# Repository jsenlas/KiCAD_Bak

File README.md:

# KiCAD_Bak
Bachelor thesis HW section - KiCAD

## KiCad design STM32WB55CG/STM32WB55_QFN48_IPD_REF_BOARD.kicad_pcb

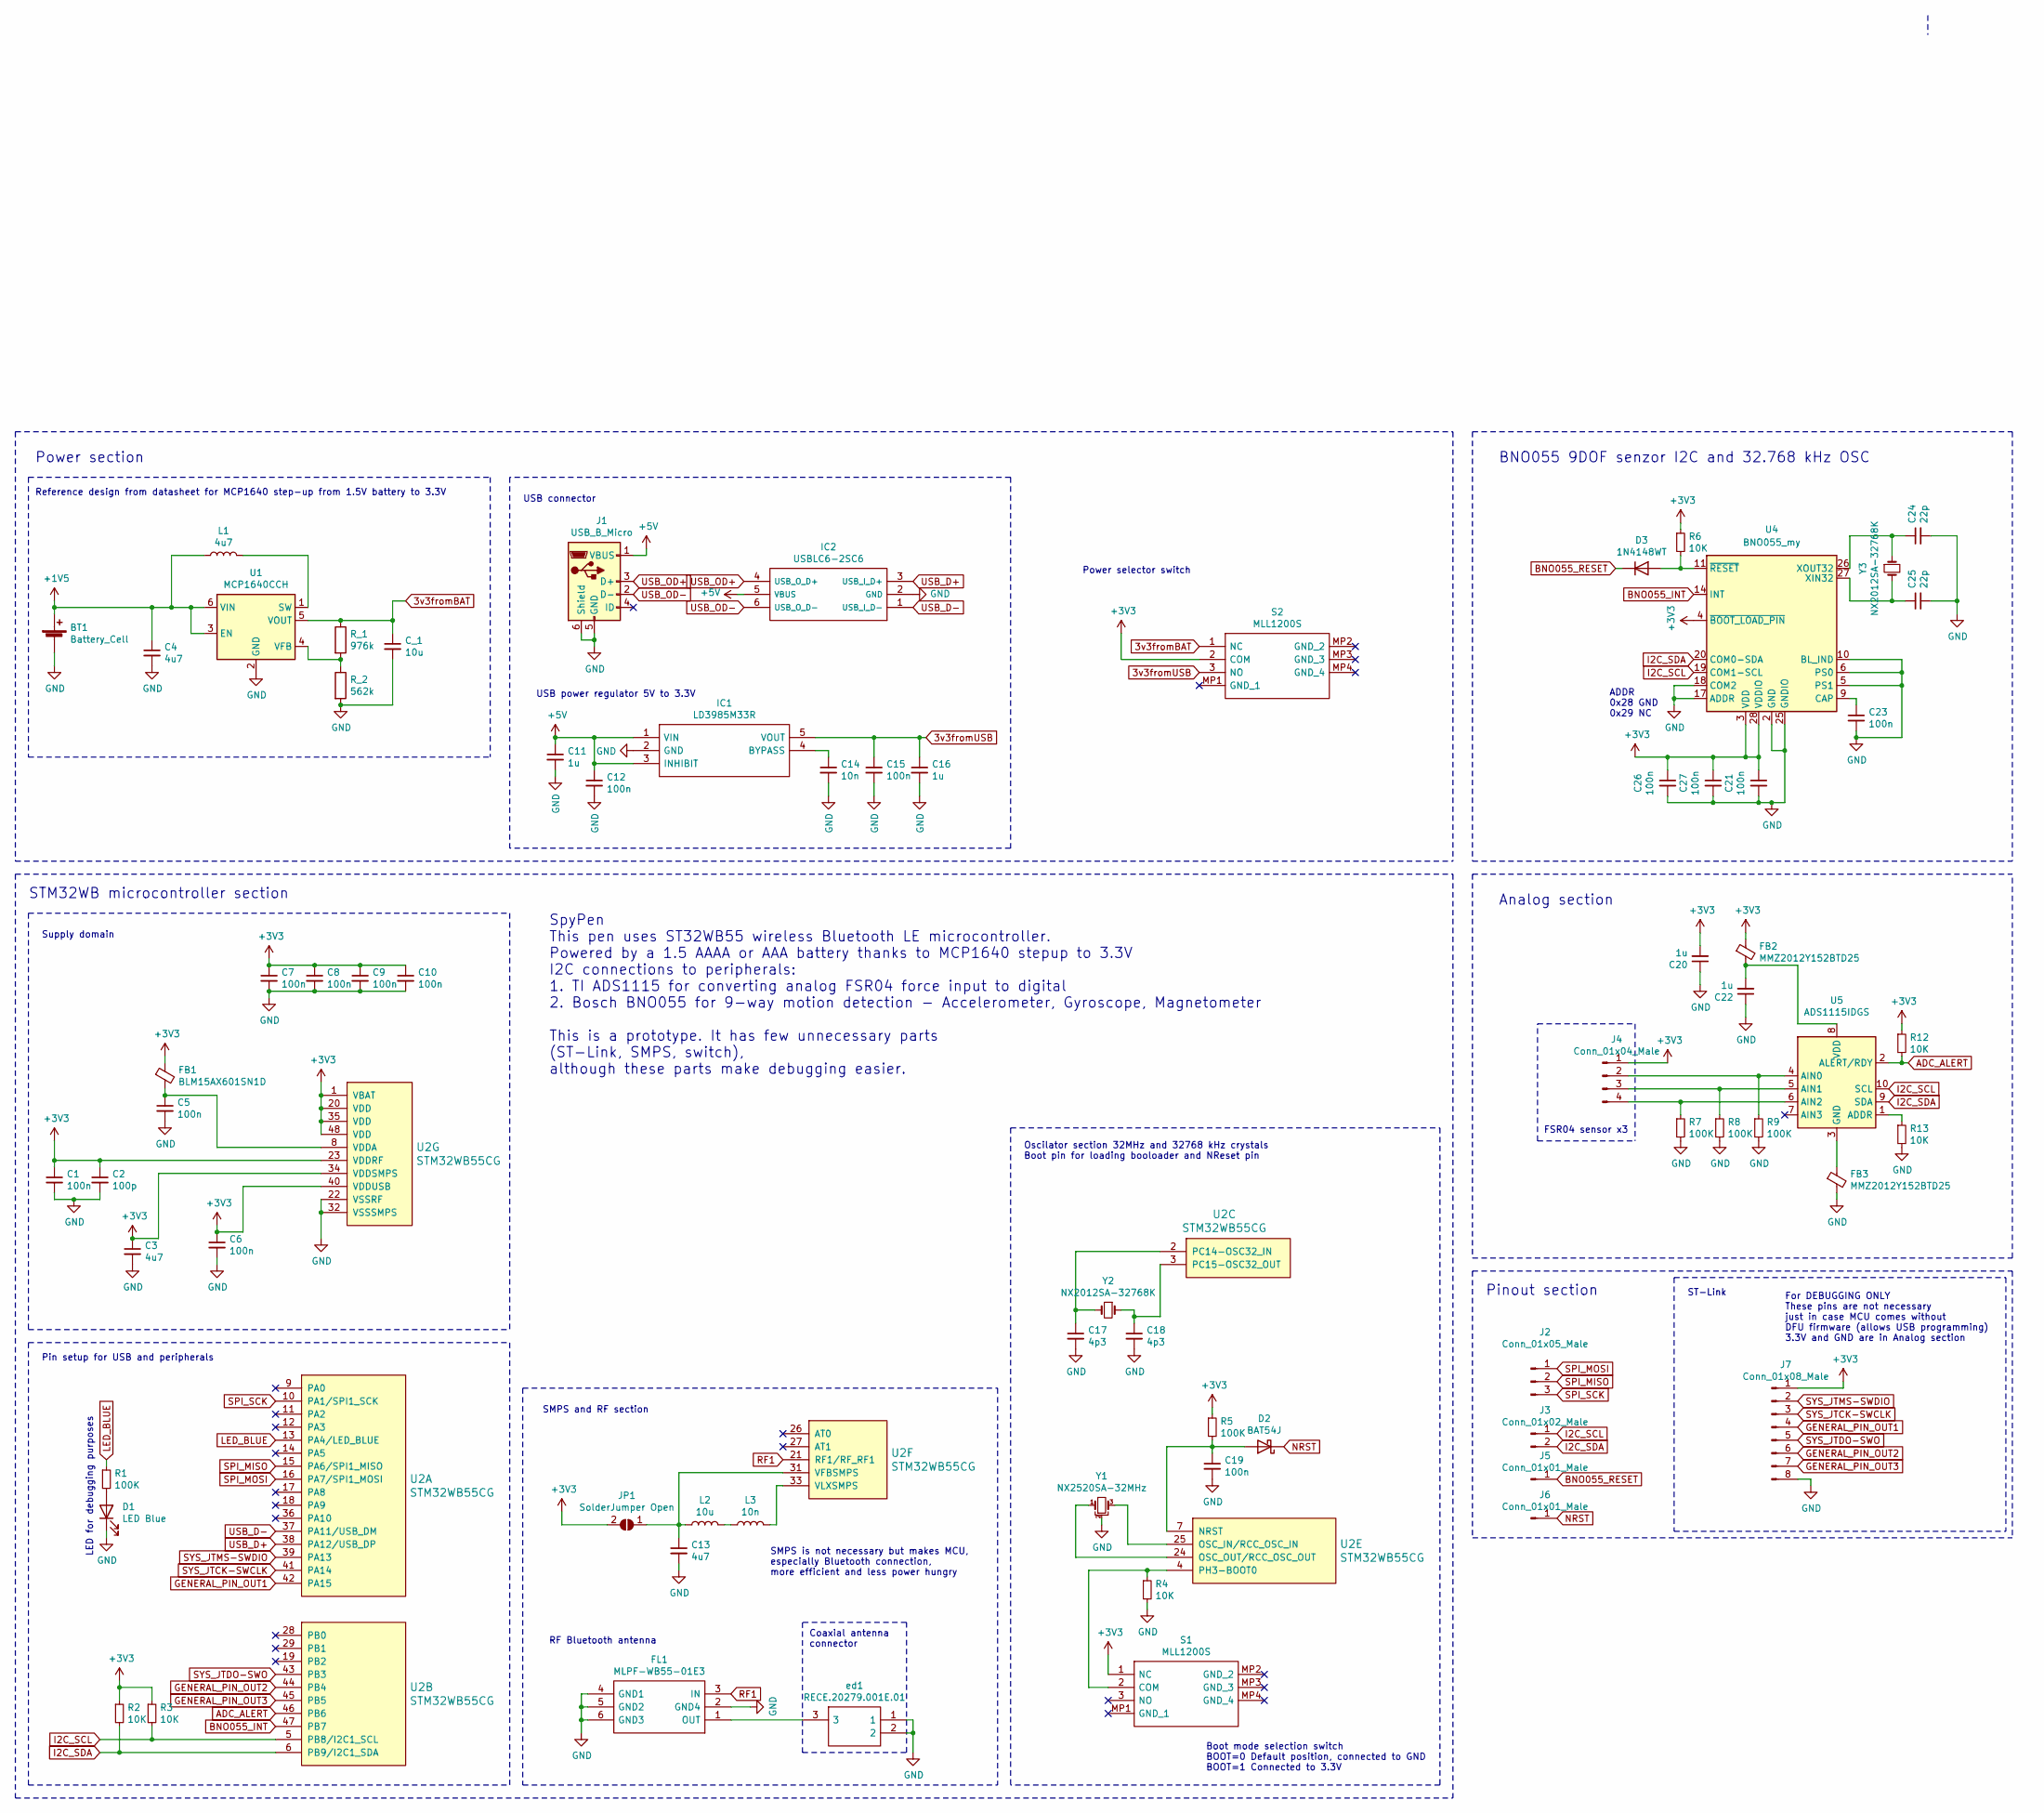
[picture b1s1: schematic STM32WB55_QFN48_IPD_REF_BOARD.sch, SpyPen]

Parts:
BT1: Battery_Cell; battery_connector_narrow
C1, C5, C6, C7, C8, C9, C10, C15, C19, C21, C23, C26, C27: 100n; C_0402_1005Metric
C2: 100p; C_0402_1005Metric
C3, C4, C13: 4u7; C_0402_1005Metric
C11, C16, C20, C22: 1u; C_0402_1005Metric
C12: 100n; C_0603_1608Metric
C14: 10n; C_0402_1005Metric
C17, C18: 4p3; C_0402_1005Metric
C24, C25: 22p; C_0402_1005Metric
C_1: 10u; C_0402_1005Metric
D1: LED Blue; LED_0603_1608Metric
D2: BAT54J; D_SOD-323F
D3: 1N4148WT; D_SOD-523
FB1: BLM15AX601SN1D; R_0402_1005Metric
FB2, FB3: MMZ2012Y152BTD25; R_0402_1005Metric
FL1: MLPF-WB55-01E3; MLPF-WB55-02E3; Manufacturer_Part_Number MLPF-WB55-01E3; Mouser Part Number 511-MLPF-WB55-01E3
IC1: LD3985M33R; SOT-23-5; Manufacturer_Part_Number LD3985M33R; Mouser Part Number 511-LD3985M33R
IC2: USBLC6-2SC6; SOT-23-6; Manufacturer_Part_Number USBLC6-2SC6; Mouser Part Number 511-USBLC6-2SC6
J1: USB_B_Micro; UB-MC5BR3-SDWP604-4S-TF
J2: Conn_01x05_Male; pin_03
J3: Conn_01x02_Male; pin_02
J4: Conn_01x04_Male; Pin_FSR
J5, J6: Conn_01x01_Male; pin_01
J7: Conn_01x08_Male; pin_08
JP1: SolderJumper Open; SolderJumper-2_P1.3mm_Open_TrianglePad1.0x1.5mm
L1: 4u7; L_0603_1608Metric
L2: 10u; L_0712_SMD
L3: 10n; L_0603_1608Metric
R1, R5, R7, R8, R9: 100K; R_0402_1005Metric
R2, R3, R4, R6, R12, R13: 10K; R_0402_1005Metric
R_1: 976k; R_0402_1005Metric
R_2: 562k; R_0402_1005Metric
S1, S2: MLL1200S; Manufacturer_Part_Number MLL1200S; Mouser Part Number 506-MLL1200S
U1: MCP1640CCH; SOT-23-6
U2: STM32WB55CG; STM32WB55CGU7
U4: BNO055_my; LGA-28_5.2x3.8mm_P0.5mm
U5: ADS1115IDGS; ADS1115IRUGR
Y1: NX2520SA-32MHz; Crystal_SMD_2520-4Pin_2.5x2.0mm
Y2, Y3: NX2012SA-32768K; Crystal_2012_custom
ed1: RECE.20279.001E.01; Manufacturer_Part_Number RECE.20279.001E.01; Mouser Part Number N/A

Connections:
3v3fromBAT: C_1.1, R_1.1, S2.1 (NC), U1.5 (VOUT)
3v3fromUSB: C15.1, C16.1, IC1.5 (VOUT), S2.3 (NO)
+1V5: BT1.1 (+), C4.1, L1.1, U1.3 (EN), U1.6 (VIN)
+3V3: C1.1, C2.1, C3.1, C6.1, C7.1, C8.1, C9.1, C10.1, C20.2, C21.1, C26.1, C27.1, FB1.1, FB2.1, J4.1, J7.1, JP1.2 (B), R2.1, R3.1, R5.1, R6.1, R12.1, S1.1 (NC), S2.2 (COM), U2.1 (VBAT), U2.20 (VDD), U2.23 (VDDRF), U2.34 (VDDSMPS), U2.35 (VDD), U2.40 (VDDUSB), U2.48 (VDD), U4.3 (VDD), U4.4 (~BOOT_LOAD_PIN), U4.28 (VDDIO)
+5V: C11.1, C12.1, IC1.1 (VIN), IC1.3 (INHIBIT), IC2.5 (VBUS), J1.1 (VBUS)
ADC_ALERT: R12.2, U2.46 (PB6), U5.2 (ALERT/RDY)
BNO055_INT: U2.47 (PB7), U4.14 (INT)
BNO055_RESET: D3.1 (K), J5.1
GENERAL_PIN_OUT1: J7.4, U2.42 (PA15)
GENERAL_PIN_OUT2: J7.6, U2.44 (PB4)
GENERAL_PIN_OUT3: J7.7, U2.45 (PB5)
GND: BT1.2 (-), C1.2, C2.2, C3.2, C4.2, C5.2, C6.2, C7.2, C8.2, C9.2, C10.2, C11.2, C12.2, C13.2, C14.2, C15.2, C16.2, C17.2, C18.2, C19.2, C20.1, C21.2, C22.1, C23.2, C24.2, C25.2, C26.2, C27.2, C_1.2, D1.1 (K), FB3.2, FL1.2 (GND4), FL1.4 (GND1), FL1.5 (GND2), FL1.6 (GND3), IC1.2 (GND), IC2.2 (GND), J1.5 (GND), J1.6 (Shield), J7.8, R4.2, R7.2, R8.2, R9.2, R13.2, R_2.2, U1.2 (GND), U2.22 (VSSRF), U2.32 (VSSSMPS), U2.49, U4.2 (GND), U4.5 (PS1), U4.6 (PS0), U4.10 (BL_IND), U4.15 (GNDIO), U4.16 (GNDIO), U4.17 (ADDR), U4.18 (COM2), U4.25 (GNDIO), Y1.2, Y1.4, ed1.1, ed1.2
I2C_SCL: J3.1, R3.2, U2.5 (PB8/I2C1_SCL), U4.19 (COM1-SCL), U5.10 (SCL)
I2C_SDA: J3.2, R2.2, U2.6 (PB9/I2C1_SDA), U4.20 (COM0-SDA), U5.9 (SDA)
LED_BLUE: R1.1, U2.13 (PA4/LED_BLUE)
NRST: D2.1 (K), J6.1
unnamed: C5.1, FB1.2, U2.8 (VDDA)
unnamed: C13.1, JP1.1 (A), L2.1, U2.31 (VFBSMPS)
unnamed: C14.1, IC1.4 (BYPASS)
unnamed: C17.1, U2.2 (PC14-OSC32_IN), Y2.2
unnamed: C18.1, U2.3 (PC15-OSC32_OUT), Y2.1
unnamed: C19.1, D2.2 (A), R5.2, U2.7 (NRST)
unnamed: C22.2, FB2.2, U5.8 (VDD)
unnamed: C23.1, U4.9 (CAP)
unnamed: C24.1, U4.26 (XOUT32), Y3.1
unnamed: C25.1, U4.27 (XIN32), Y3.2
unnamed: D1.2 (A), R1.2
unnamed: D3.2 (A), R6.2, U4.11 (~RESET)
unnamed: FB3.1, U5.3 (GND)
unnamed: FL1.1 (OUT), ed1.3
unnamed: J4.2, R9.1, U5.4 (AIN0)
unnamed: J4.3, R8.1, U5.5 (AIN1)
unnamed: J4.4, R7.1, U5.6 (AIN2)
unnamed: L1.2, U1.1 (SW)
unnamed: L2.2, L3.1
unnamed: L3.2, U2.33 (VLXSMPS)
unnamed: R4.1, S1.2 (COM), U2.4 (PH3-BOOT0)
unnamed: R13.1, U5.1 (ADDR)
unnamed: R_1.2, R_2.1, U1.4 (VFB)
unnamed: U2.24 (OSC_OUT/RCC_OSC_OUT), Y1.1
unnamed: U2.25 (OSC_IN/RCC_OSC_IN), Y1.3
RF1: FL1.3 (IN), U2.21 (RF1/RF_RF1)
SPI_MISO: J2.2, U2.15 (PA6/SPI1_MISO)
SPI_MOSI: J2.1, U2.16 (PA7/SPI1_MOSI)
SPI_SCK: J2.3, U2.10 (PA1/SPI1_SCK)
SYS_JTCK-SWCLK: J7.3, U2.41 (PA14)
SYS_JTDO-SWO: J7.5, U2.43 (PB3)
SYS_JTMS-SWDIO: J7.2, U2.39 (PA13)
USB_D+: IC2.3 (USB_I_D+), U2.38 (PA12/USB_DP)
USB_D-: IC2.1 (USB_I_D-), U2.37 (PA11/USB_DM)
USB_OD+: IC2.4 (USB_O_D+), J1.3 (D+)
USB_OD-: IC2.6 (USB_O_D-), J1.2 (D-)

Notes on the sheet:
Analog section
USB connector
RF Bluetooth antenna
Supply domain
Oscilator section 32MHz and 32768 kHz crystals Boot pin for loading booloader and NReset pin
Pin setup for USB and peripherals
SMPS and RF section
Reference design from datasheet for MCP1640 step-up from 1.5V battery to 3.3V
USB power regulator 5V to 3.3V
Boot mode selection switch BOOT=0 Default position, connected to GND BOOT=1 Connected to 3.3V
LED for debugging purposes
Coaxial antenna connector
BNO055 9DOF senzor I2C and 32.768 kHz OSC
Pinout section
FSR04 sensor x3
For DEBUGGING ONLY These pins are not necessary just in case MCU comes without DFU firmware (allows USB programming) 3.3V and GND are in Analog section
ST-Link
SMPS is not necessary but makes MCU, especially Bluetooth connection, more efficient and less power hungry
STM32WB microcontroller section
Power section
Power selector switch
SpyPen This pen uses ST32WB55 wireless Bluetooth LE microcontroller. Powered by a 1.5 AAAA or AAA battery thanks to MCP1640 stepup to 3.3V I2C connections to peripherals: 1. TI ADS1115 for converting analog FSR04 force input to digital 2. Bosch BNO055 for 9-way motion detection - Accelerometer, Gyr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
ADDR 0x28 GND 0x29 NC

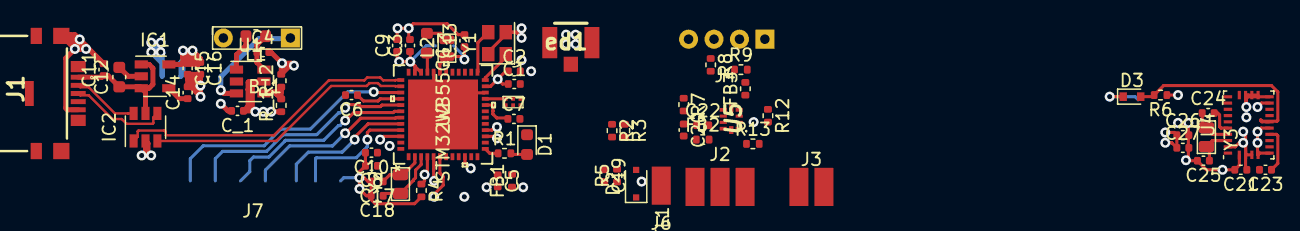
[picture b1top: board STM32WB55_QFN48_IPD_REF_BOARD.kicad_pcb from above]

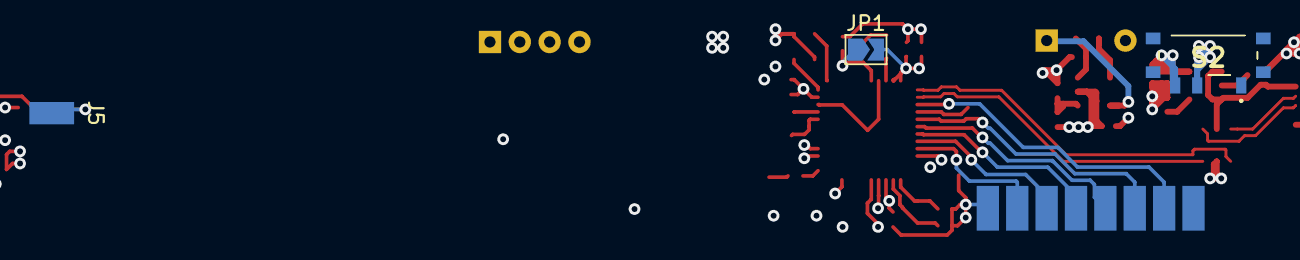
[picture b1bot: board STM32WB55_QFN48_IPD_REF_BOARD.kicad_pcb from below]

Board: 4 copper layers, 71 parts (3 on the bottom side), 52 nets.

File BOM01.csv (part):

"Source:","/home/jakub/VUT_FIT/bakalarka2.0/KiCAD_Bak/STM32WB55CG/STM32WB55_QFN48_IPD_REF_BOARD.sch"
"Date:","Wed 17 Feb 2021 11:01:06 PM CET"
"Tool:","Eeschema 5.1.9-1.fc32"
"Component Count:","70"
"Ref","Value","Footprint","Datasheet","Manufacturer","Vendor"
"BT1","Battery_Cell","0Pretty:battery_connector","~","",""
"C1","100n","Capacitor_SMD:C_0402_1005Metric","https://www.mouser.sk/ProductDetail/Yageo/CC0402JRX7R8BB104/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","",""
"C2","100p","Capacitor_SMD:C_0402_1005Metric","https://www.mouser.sk/ProductDetail/AVX/04026C101KAT2A/?qs=n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","",""
"C3","4u7","Capacitor_SMD:C_0402_1005Metric","https://www.mouser.sk/ProductDetail/Murata-Electronics/GRT15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","",""
"C4","4u7","Capacitor_SMD:C_0402_1005Metric","https://www.mouser.sk/ProductDetail/Murata-Electronics/GRT15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","",""
"C5","100n","Capacitor_SMD:C_0402_1005Metric","https://www.mouser.sk/ProductDetail/Yageo/CC0402JRX7R8BB104/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","",""
"C6","100n","Capacitor_SMD:C_0402_1005Metric","https://www.mouser.sk/ProductDetail/Yageo/CC0402JRX7R8BB104/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","",""
"C7","100n","Capacitor_SMD:C_0402_1005Metric","https://www.mouser.sk/ProductDetail/Yageo/CC0402JRX7R8BB104/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","",""
"C8","100n","Capacitor_SMD:C_0402_1005Metric","https://www.mouser.sk/ProductDetail/Yageo/CC0402JRX7R8BB104/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","",""
"C9","100n","Capacitor_SMD:C_0402_1005Metric","https://www.mouser.sk/ProductDetail/Yageo/CC0402JRX7R8BB104/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","",""
"C10","100n","Capacitor_SMD:C_0402_1005Metric","https://www.mouser.sk/ProductDetail/Yageo/CC0402JRX7R8BB104/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","",""
"C11","1u","Capacitor_SMD:C_0402_1005Metric","https://www.mouser.sk/ProductDetail/Taiyo-Yuden/LMK105BJ105M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","",""
"C12","100n","Capacitor_SMD:C_0603_1608Metric","https://www.mouser.sk/ProductDetail/Yageo/CC0201KRX6S6BB104/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","",""
"C13","4u7","Capacitor_SMD:C_0402_1005Metric","https://www.mouser.sk/ProductDetail/Murata-Electronics/GRT15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","",""
"C14","10n","Capacitor_SMD:C_0402_1005Metric","https://www.mouser.sk/ProductDetail/Murata-Electronics/GCB15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","",""
"C15","100n","Capacitor_SMD:C_0402_1005Metric","https://www.mouser.sk/ProductDetail/AVX/04026D104KAT2A/?qs=L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","",""
"C16","1u","Capacitor_SMD:C_0402_1005Metric","https://www.mouser.sk/ProductDetail/Taiyo-Yuden/LMK105BJ105M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","",""
"C17","4p3","Capacitor_SMD:C_0402_1005Metric","https://www.mouser.sk/ProductDetail/KEMET/C0402C439B5GACTU/?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","",""
"C18","4p3","Capacitor_SMD:C_0402_1005Metric","https://www.mouser.sk/ProductDetail/KEMET/C0402C439B5GACTU/?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","",""
"C19","100n","Capacitor_SMD:C_0402_1005Metric","https://www.mouser.sk/ProductDetail/Yageo/CC0402JRX7R8BB104/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","",""
"C20","1u","Capacitor_SMD:C_0402_1005Metric","https://www.mouser.sk/ProductDetail/Murata-Electronics/GRT15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","",""
"C21","100n","Capacitor_SMD:C_0402_1005Metric","https://www.mouser.sk/ProductDetail/Yageo/CC0402JRX7R8BB104/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","",""
"C22","1u","Capacitor_SMD:C_0402_1005Metric","https://www.mouser.sk/ProductDetail/Murata-Electronics/GRT15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","",""
"C23","1u","Capacitor_SMD:C_0402_1005Metric","https://www.mouser.sk/ProductDetail/Murata-Electronics/GRT15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","",""
"C24","22p","Capacitor_SMD:C_0402_1005Metric","https://www.mouser.sk/ProductDetail/KEMET/C0402C220J5GAC7411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","",""
"C25","22p","Capacitor_SMD:C_0402_1005Metric","https://www.mouser.sk/ProductDetail/KEMET/C0402C220J5GAC7411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","",""
"C_1","10u","Capacitor_SMD:C_0402_1005Metric","https://www.mouser.sk/ProductDetail/Murata-Electronics/GRJ15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","",""
"D1","LED Blue","LED_SMD:LED_0402_1005Metric","https://www.mouser.sk/ProductDetail/ROHM-Semiconductor/SMLP1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","",""
"D2","BAT54J","Diode_SMD:D_SOD-323F","https://assets.nexperia.com/documents/data-sheet/BAT54J.pdf","",""
"D3","1N4148WT","Diode_SMD:D_SOD-523","https://www.diodes.com/assets/Datasheets/ds30396.pdf","",""
"ed1","RECE.20279.001E.01","RECE_antena_connector:RECE.20279.001E.01","http://www.taoglas.com/wp-content/uploads/2016/04/RECE.20279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","",""
"FB1","Z0805C601BSMST","Resistor_SMD:R_0805_2012Metric","https://www.mouser.sk/ProductDetail/KEMET/Z0805C601BSMST/?qs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","",""
"FB2","MMZ2012Y152BTD25","Resistor_SMD:R_0805_2012Metric","https://www.mouser.sk/ProductDetail/TDK/MMZ2012Y152BTD25?qs=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","",""
"FB3","MMZ2012Y152BTD25","Resistor_SMD:R_0805_2012Metric","https://www.mouser.sk/ProductDetail/TDK/MMZ2012Y152BTD25?qs=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","",""
"FL1","MLPF-WB55-01E3","0Pretty:MLPF-WB55-02E3","https://www.st.com/resource/en/datasheet/mlpf-wb55-01e3.pdf","",""
"IC1","LD3985M33R","Package_TO_SOT_SMD:SOT-23-5","http://www.st.com/st-web-ui/static/active/en/resource/techni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","",""
"IC2","USBLC6-2SC6","Package_TO_SOT_SMD:SOT-23-6","http://www.st.com/st-web-ui/static/active/en/resource/techni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","",""
"J1","USB_B_Micro","microUSB:UB-MC5BR3-SDWP604-4S-TF","https://www.tme.eu/Document/7505dce1b4a576fb38a063ffeef6b4eb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","",""
"J2","Conn_01x06_Male","Molexkonektor:55932-0610","~","",""
"J3","Conn_01x03_Male","0Pretty:PCB_Pin_connector","~","",""
"J4","Conn_01x04_Male","0Pretty:Pin_FSR","~","",""
"J5","Conn_01x06_Male","Molexkonektor:55932-0610","~","",""
"JP1","SolderJumper Open","Jumper:SolderJumper-2_P1.3mm_Open_TrianglePad1.0x1.5mm","~","",""
"L1","4u7","Inductor_SMD:L_0603_1608Metric","https://www.mouser.sk/ProductDetail/TDK/MLZ1608E4R7MT/?qs=h0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","",""
"L2","10u","0Pretty:L_0712_SMD","https://www.mouser.sk/ProductDetail/Bourns/PM0603-10NJ-RC/?q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","",""
"L3","10n","Inductor_SMD:L_0603_1608Metric","https://www.mouser.sk/ProductDetail/KEMET/L0603C10NJRMST/?qs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","",""
"R1","100K","Resistor_SMD:R_0402_1005Metric","https://www.mouser.sk/ProductDetail/Welwyn-Components-TT-Ele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","",""
"R2","10K","Resistor_SMD:R_0402_1005Metric","https://www.mouser.sk/ProductDetail/Vishay-Dale/CRCW040210K0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","",""
"R3","10K","Resistor_SMD:R_0402_1005Metric","https://www.mouser.sk/ProductDetail/Vishay-Dale/CRCW040210K0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","",""
"R4","10K","Resistor_SMD:R_0402_1005Metric","https://www.mouser.sk/ProductDetail/Vishay-Dale/CRCW040210K0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","",""
"R5","100K","Resistor_SMD:R_0402_1005Metric","https://www.mouser.sk/ProductDetail/Welwyn-Components-TT-Ele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","",""
"R6","10K","Resistor_SMD:R_0402_1005Metric","https://www.mouser.sk/ProductDetail/Vishay-Dale/CRCW040210K0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","",""
"R7","100K","Resistor_SMD:R_0402_1005Metric","https://www.mouser.sk/ProductDetail/Welwyn-Components-TT-Ele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","",""
"R8","100K","Resistor_SMD:R_0402_1005Metric","https://www.mouser.sk/ProductDetail/Welwyn-Components-TT-Ele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","",""
"R9","100K","Resistor_SMD:R_0402_1005Metric","https://www.mouser.sk/ProductDetail/Welwyn-Components-TT-Ele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","",""
"R10","10K","Resistor_SMD:R_0402_1005Metric","https://www.mouser.sk/ProductDetail/Vishay-Dale/CRCW040210K0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","",""
"R11","10K","Resistor_SMD:R_0402_1005Metric","https://www.mouser.sk/ProductDetail/Vishay-Dale/CRCW040210K0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","",""
"R12","10K","Resistor_SMD:R_0402_1005Metric","https://www.mouser.sk/ProductDetail/Vishay-Dale/CRCW040210K0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","",""
"R13","10K","Resistor_SMD:R_0402_1005Metric","https://www.mouser.sk/ProductDetail/Vishay-Dale/CRCW040210K0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","",""
"R_1","976k","Resistor_SMD:R_0402_1005Metric","https://www.mouser.sk/ProductDetail/Vishay-Dale/CRCW0402976K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","",""
"R_2","562k","Resistor_SMD:R_0402_1005Metric","https://www.mouser.sk/ProductDetail/Vishay-Dale/CRCW0402562K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","",""
"S1","MLL1200S","vypinac:MLL1200S","https://www.te.com/commerce/DocumentDelivery/DDEController?A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","",""
"S2","MLL1200S","vypinac:MLL1200S","https://www.te.com/commerce/DocumentDelivery/DDEController?A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","",""
"U1","MCP1640CCH","Package_TO_SOT_SMD:SOT-23-6","http://ww1.microchip.com/downloads/en/DeviceDoc/20002234D.pdf","",""
"U2","STM32WB55CG","ST32_3D:STM32WB55CGU7","https://www.mouser.sk/datasheet/2/389/stm32wb55cc-1588841.pdf","",""
"U4","BNO055_my","Package_LGA:LGA-28_5.2x3.8mm_P0.5mm","https://www.mouser.sk/datasheet/2/783/BST_BNO055_DS000-1509603.pdf","",""
"U5","ADS1115IDGS","ADS1115:ADS1115IRUGR","http://www.ti.com/lit/ds/symlink/ads1113.pdf","",""
"Y1","NX2520SA-32MHz","Crystal:Crystal_SMD_2520-4Pin_2.5x2.0mm","https://www.mouser.sk/ProductDetail/NDK/NX2520SA-32000M-STD-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","",""
"Y2","NX2012SA-32768K","0Pretty:Crystal_2012_custom","https://cz.mouser.com/ProductDetail/NDK/NX2012SA-32768K-STD-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","",""
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
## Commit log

2021-01-27 initial
2021-02-12 schema complete
2021-02-17 assign footprints complete need one more look and a check from Simek
2021-02-25 dokoncene rozlozenie okolo STM32WB podla referencneho dizajnu
2021-03-03 in the middle of moving libs

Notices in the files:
STM32WB55CG/STM32WB55_QFN48_IPD_REF_BOARD.sch:
creativecommons.org/licenses/by/4.0
License: CC BY 4.0
parts and their libraries:
Copyright 2016 Accelerated Designs. All rights reserved.
